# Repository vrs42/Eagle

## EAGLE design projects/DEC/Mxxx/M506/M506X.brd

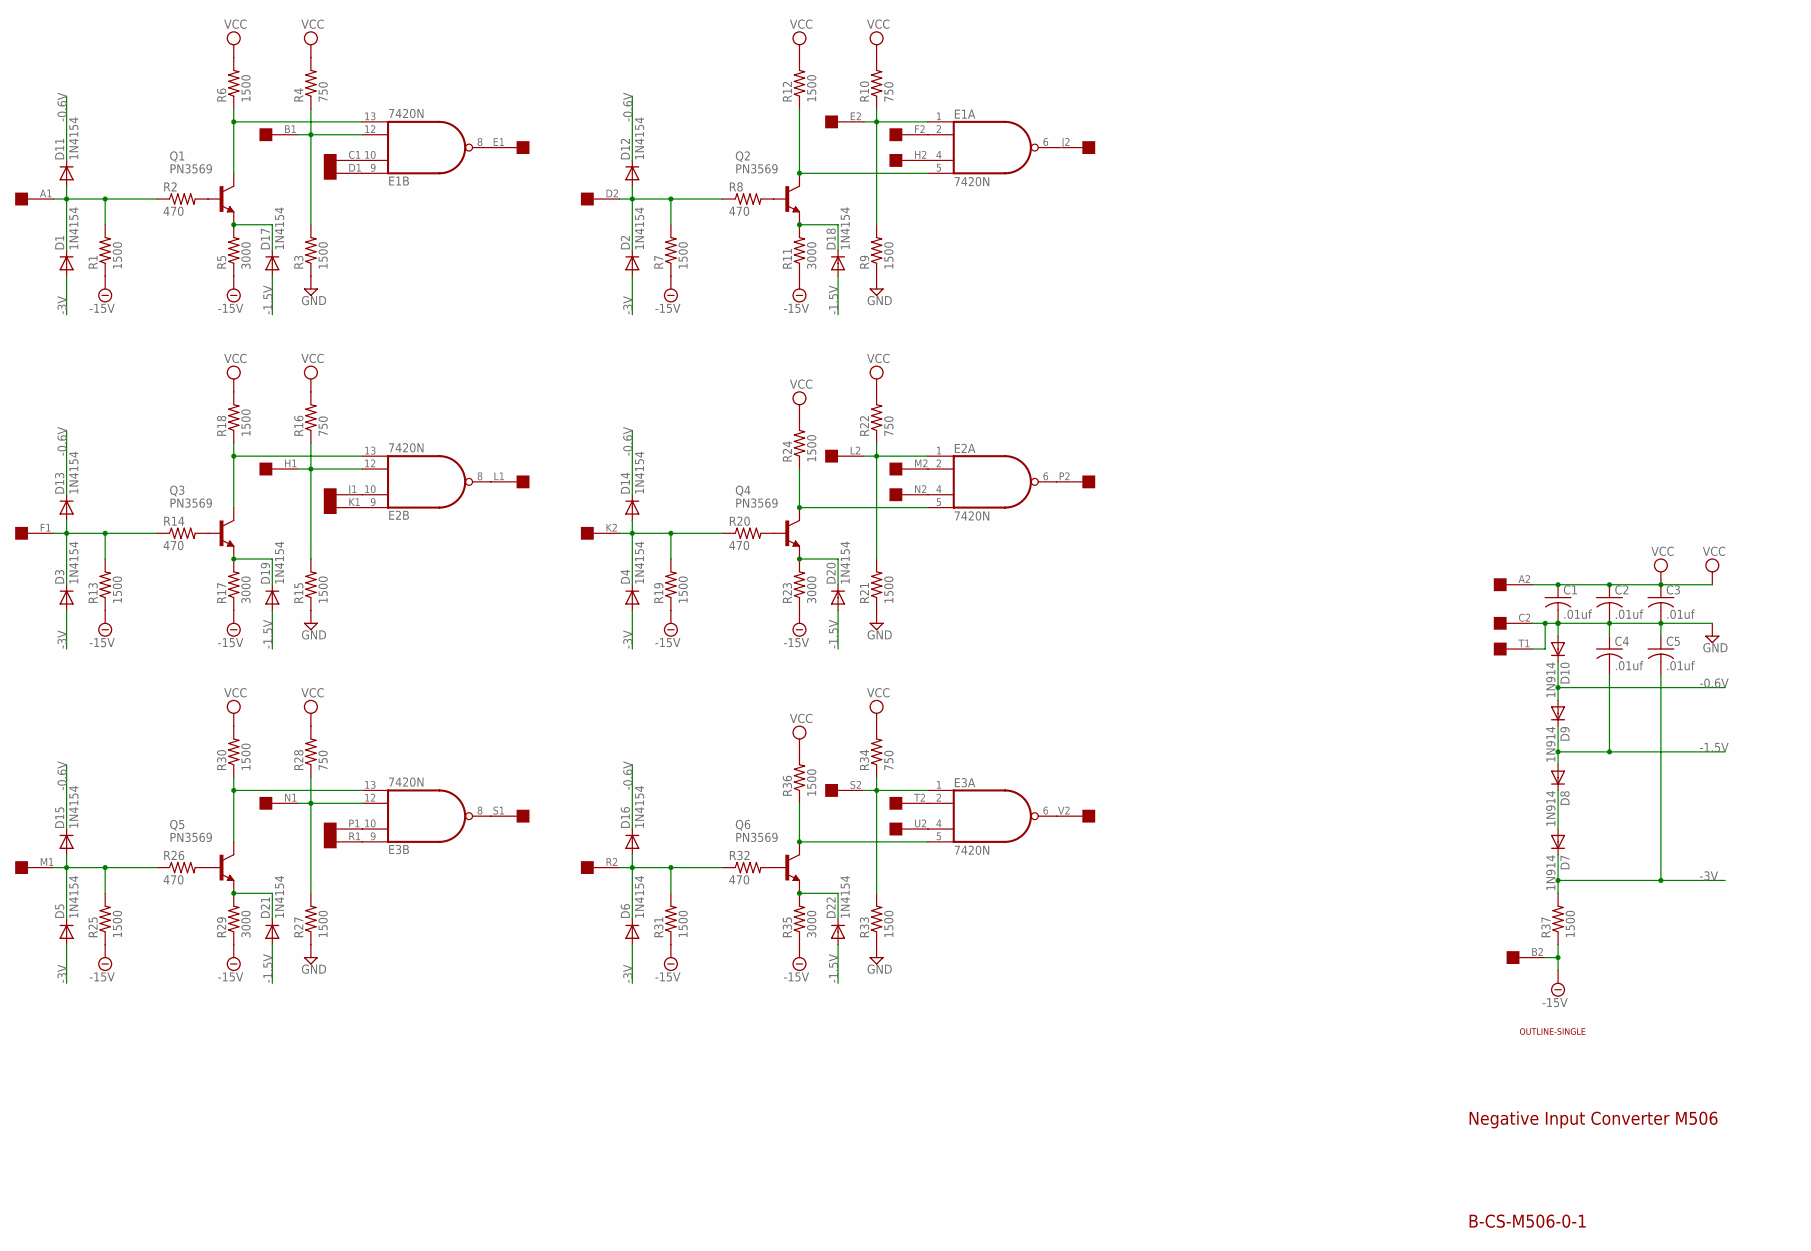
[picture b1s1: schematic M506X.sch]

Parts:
C1, C2, C3, C4, C5: .01uf; C050-025X075
D1, D2, D3, D4, D5, D6, D11, D12, D13, D14, D15, D16, D17, D18, D19, D20, D21, D22: 1N4154; DO35-10
D7, D8, D9, D10: 1N914; DO35-10
E1, E2, E3: 7420N; DIL14
Q1, Q2, Q3, Q4, Q5, Q6: PN3569; TO39
R1, R3, R6, R7, R9, R12, R13, R15, R18, R19, R21, R24, R25, R27, R30, R31, R33, R36, R37: 1500; 0207/10
R2, R8, R14, R20, R26, R32: 470; 0207/10
R4, R10, R16, R22, R28, R34: 750; 0207/10
R5, R11, R17, R23, R29, R35: 3000; 0207/10
U$2: SINGLE; EDGE-CON2
U$4: OUTLINE-SINGLE; SINGLE

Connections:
-0.6V: D9.A, D10.C, D11.C, D12.C, D13.C, D14.C, D15.C, D16.C
-1.5V: C4.2, D8.A, D9.C, D17.A, D18.A, D19.A, D20.A, D21.A, D22.A
-3V: C5.2, D1.A, D2.A, D3.A, D4.A, D5.A, D6.A, D7.C, R37.2
-15V: R1.1, R5.1, R7.1, R11.1, R13.1, R17.1, R19.1, R23.1, R25.1, R29.1, R31.1, R35.1, R37.1, U$2.B2
GND: C1.2, C2.2, C3.2, C4.1, C5.1, D10.A, E1.7 (GND), E2.7 (GND), E3.7 (GND), R3.1, R9.1, R15.1, R21.1, R27.1, R33.1, U$2.C2, U$2.T1
unnamed: D1.C, D11.A, R1.2, R2.1, U$2.A1
unnamed: Q1.2 (B), R2.2
unnamed: D17.C, Q1.1 (E), R5.2
unnamed: E1.12 (I2), R3.2, R4.1, U$2.B1
unnamed: E1.13 (I3), Q1.3 (C), R6.1
unnamed: E1.10 (I1), U$2.C1
unnamed: E1.9 (I0), U$2.D1
unnamed: E1.8 (O), U$2.E1
unnamed: D2.C, D12.A, R7.2, R8.1, U$2.D2
unnamed: Q2.2 (B), R8.2
unnamed: D18.C, Q2.1 (E), R11.2
unnamed: E1.1 (I0), R9.2, R10.1, U$2.E2
unnamed: E1.5 (I3), Q2.3 (C), R12.1
unnamed: E1.6 (O), U$2.J2
unnamed: E1.2 (I1), U$2.F2
unnamed: E1.4 (I2), U$2.H2
unnamed: D3.C, D13.A, R13.2, R14.1, U$2.F1
unnamed: Q3.2 (B), R14.2
unnamed: D19.C, Q3.1 (E), R17.2
unnamed: E2.12 (I2), R15.2, R16.1, U$2.H1
unnamed: E2.13 (I3), Q3.3 (C), R18.1
unnamed: D5.C, D15.A, R25.2, R26.1, U$2.M1
unnamed: Q5.2 (B), R26.2
unnamed: D21.C, Q5.1 (E), R29.2
unnamed: D4.C, D14.A, R19.2, R20.1, U$2.K2
unnamed: Q4.2 (B), R20.2
unnamed: D20.C, Q4.1 (E), R23.2
unnamed: E2.1 (I0), R21.2, R22.1, U$2.L2
unnamed: E2.5 (I3), Q4.3 (C), R24.1
unnamed: E3.12 (I2), R27.2, R28.1, U$2.N1
unnamed: E3.13 (I3), Q5.3 (C), R30.1
unnamed: D6.C, D16.A, R31.2, R32.1, U$2.R2
unnamed: Q6.2 (B), R32.2
unnamed: D22.C, Q6.1 (E), R35.2
unnamed: E3.1 (I0), R33.2, R34.1, U$2.S2
unnamed: E3.5 (I3), Q6.3 (C), R36.1
unnamed: E2.10 (I1), U$2.J1
unnamed: E2.9 (I0), U$2.K1
unnamed: E3.10 (I1), U$2.P1
unnamed: E3.9 (I0), U$2.R1
unnamed: E2.8 (O), U$2.L1
unnamed: E3.8 (O), U$2.S1
unnamed: E2.2 (I1), U$2.M2
unnamed: E2.4 (I2), U$2.N2
unnamed: E2.6 (O), U$2.P2
unnamed: E3.4 (I2), U$2.U2
unnamed: E3.6 (O), U$2.V2
unnamed: E3.2 (I1), U$2.T2
unnamed: D7.A, D8.C
VCC: C1.1, C2.1, C3.1, E1.14 (VCC), E2.14 (VCC), E3.14 (VCC), R4.2, R6.2, R10.2, R12.2, R16.2, R18.2, R22.2, R24.2, R28.2, R30.2, R34.2, R36.2, U$2.A2

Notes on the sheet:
Negative Input Converter M506
B-CS-M506-0-1

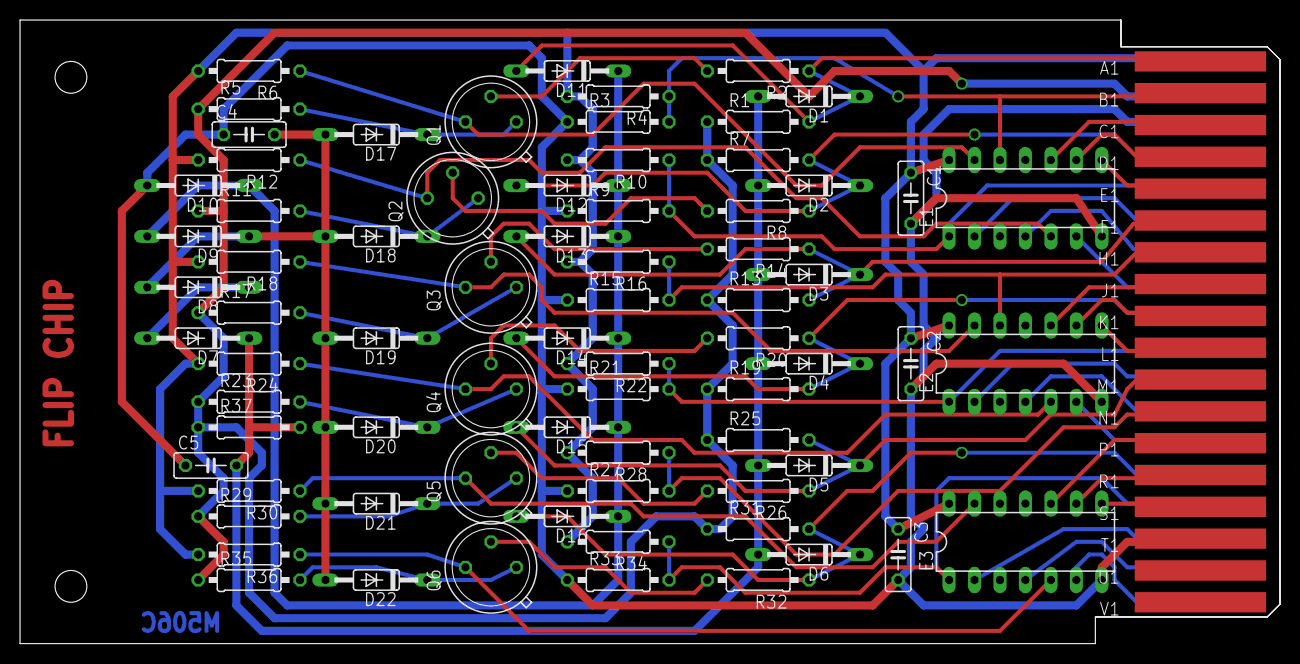
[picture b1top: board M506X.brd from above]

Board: 2 copper layers, 125.7 x 62.2 mm, 76 parts (0 on the bottom side), 55 nets.

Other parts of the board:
U$1: FLIPCHIP

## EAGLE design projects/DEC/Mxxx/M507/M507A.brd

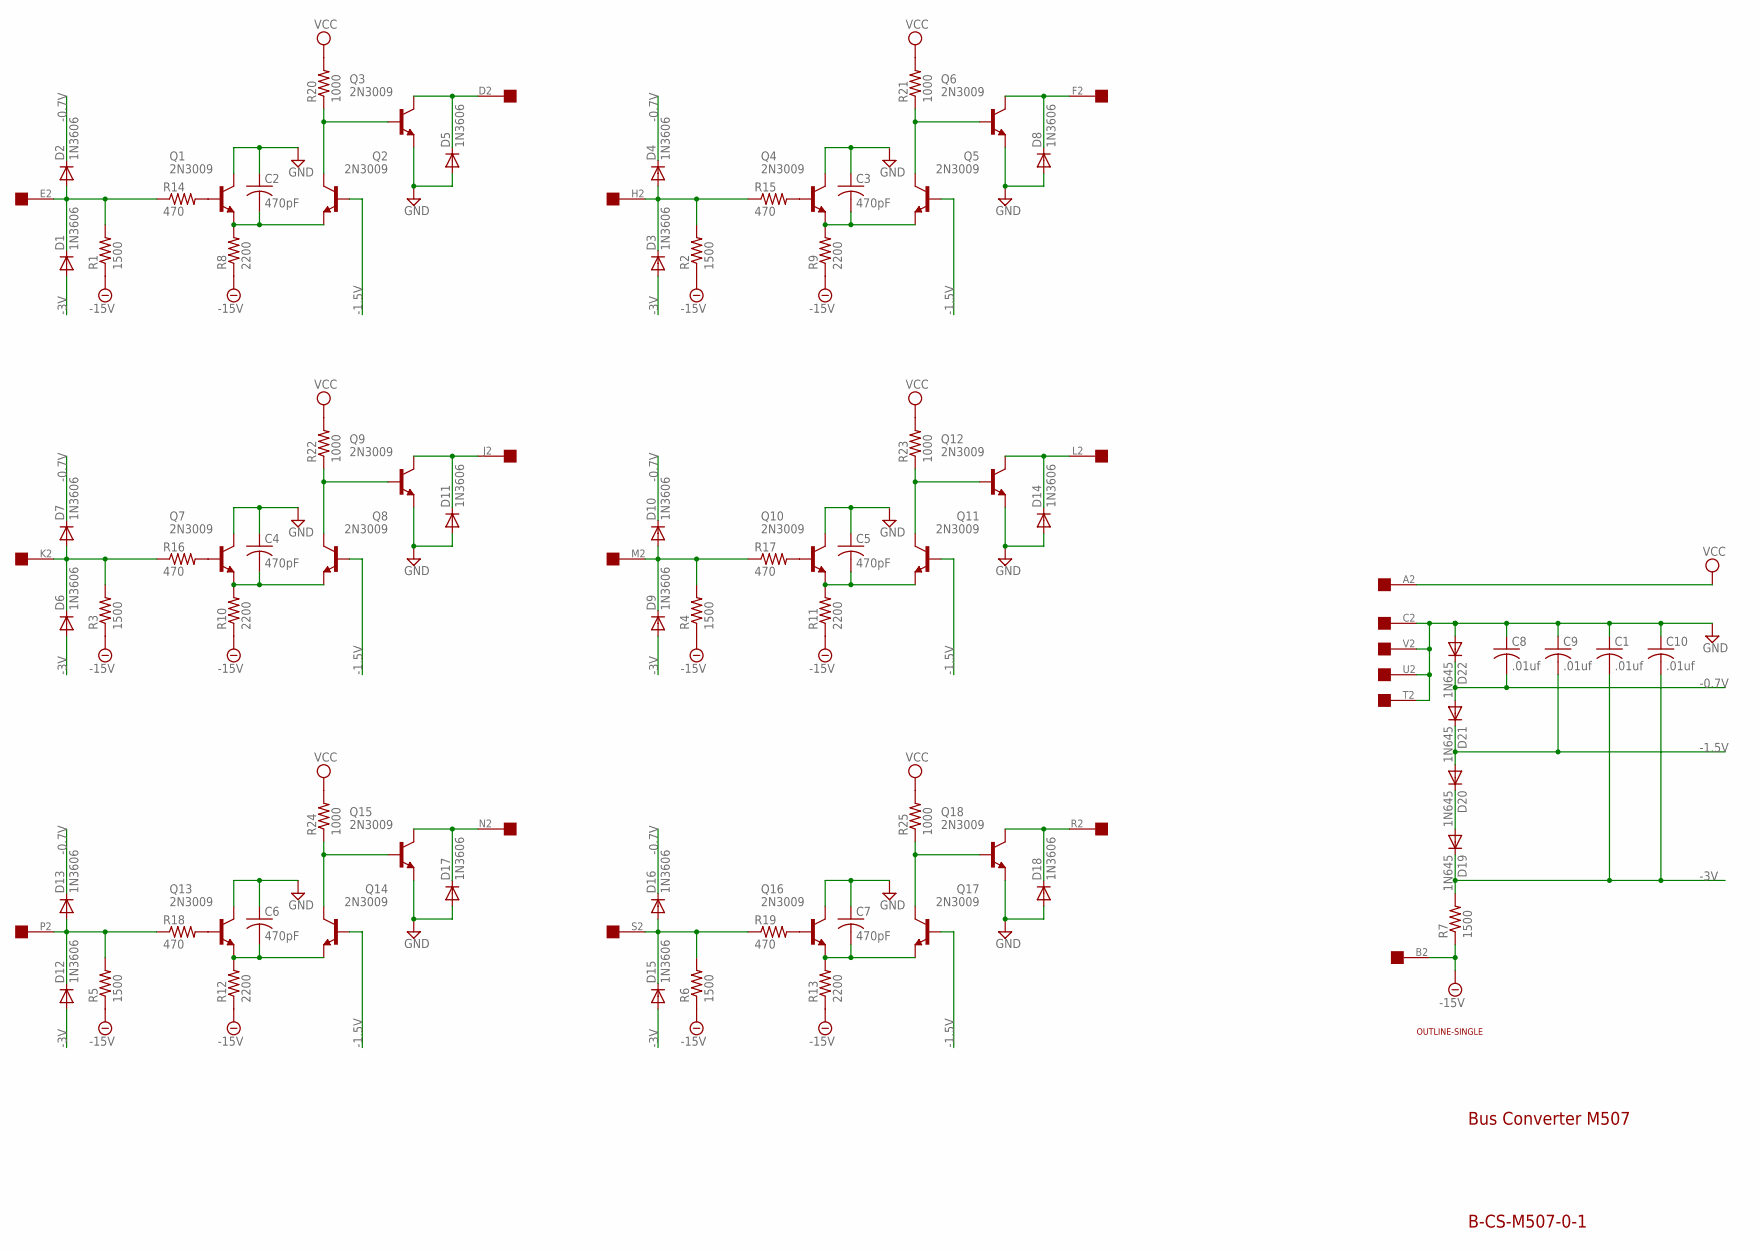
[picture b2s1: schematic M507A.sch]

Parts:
C1, C8, C9, C10: .01uf; C050-025X075
C2, C3, C4, C5, C6, C7: 470pF; C050-025X075
D1, D2, D3, D4, D5, D6, D7, D8, D9, D10, D11, D12, D13, D14, D15, D16, D17, D18: 1N3606; DO35-10
D19, D20, D21, D22: 1N645; DO35-10
Q1, Q2, Q3, Q4, Q5, Q6, Q7, Q8, Q9, Q10, Q11, Q12, Q13, Q14, Q15, Q16, Q17, Q18: 2N3009; TO39
R1, R2, R3, R4, R5, R6, R7: 1500; 0207/10
R8, R9, R10, R11, R12, R13: 2200; 0207/10
R14, R15, R16, R17, R18, R19: 470; 0207/10
R20, R21, R22, R23, R24, R25: 1000; 0207/10
U$3: EDGE-1; EDGE-CON1
U$4: OUTLINE-SINGLE; SINGLE

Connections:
-0.7V: C8.2, D2.C, D4.C, D7.C, D10.C, D13.C, D16.C, D21.A, D22.C
-1.5V: C9.2, D20.A, D21.C, Q2.2 (B), Q5.2 (B), Q8.2 (B), Q11.2 (B), Q14.2 (B), Q17.2 (B)
-3V: C1.2, C10.2, D1.A, D3.A, D6.A, D9.A, D12.A, D15.A, D19.C, R7.2
-15V: R1.1, R2.1, R3.1, R4.1, R5.1, R6.1, R7.1, R8.1, R9.1, R10.1, R11.1, R12.1, R13.1, U$3.B2
GND: C1.1, C2.1, C3.1, C4.1, C5.1, C6.1, C7.1, C8.1, C9.1, C10.1, D5.A, D8.A, D11.A, D14.A, D17.A, D18.A, D22.A, Q1.3 (C), Q3.1 (E), Q4.3 (C), Q6.1 (E), Q7.3 (C), Q9.1 (E), Q10.3 (C), Q12.1 (E), Q13.3 (C), Q15.1 (E), Q16.3 (C), Q18.1 (E), U$3.C2, U$3.T2, U$3.U2, U$3.V2
unnamed: D1.C, D2.A, R1.2, R14.1, U$3.E2
unnamed: Q1.2 (B), R14.2
unnamed: C2.2, Q1.1 (E), Q2.1 (E), R8.2
unnamed: D3.C, D4.A, R2.2, R15.1, U$3.H2
unnamed: Q2.3 (C), Q3.2 (B), R20.1
unnamed: D5.C, Q3.3 (C), U$3.D2
unnamed: Q4.2 (B), R15.2
unnamed: C3.2, Q4.1 (E), Q5.1 (E), R9.2
unnamed: Q5.3 (C), Q6.2 (B), R21.1
unnamed: D8.C, Q6.3 (C), U$3.F2
unnamed: D6.C, D7.A, R3.2, R16.1, U$3.K2
unnamed: Q7.2 (B), R16.2
unnamed: C4.2, Q7.1 (E), Q8.1 (E), R10.2
unnamed: Q8.3 (C), Q9.2 (B), R22.1
unnamed: D11.C, Q9.3 (C), U$3.J2
unnamed: D9.C, D10.A, R4.2, R17.1, U$3.M2
unnamed: Q10.2 (B), R17.2
unnamed: C5.2, Q10.1 (E), Q11.1 (E), R11.2
unnamed: Q11.3 (C), Q12.2 (B), R23.1
unnamed: D14.C, Q12.3 (C), U$3.L2
unnamed: D12.C, D13.A, R5.2, R18.1, U$3.P2
unnamed: Q13.2 (B), R18.2
unnamed: C6.2, Q13.1 (E), Q14.1 (E), R12.2
unnamed: Q14.3 (C), Q15.2 (B), R24.1
unnamed: D17.C, Q15.3 (C), U$3.N2
unnamed: D15.C, D16.A, R6.2, R19.1, U$3.S2
unnamed: Q16.2 (B), R19.2
unnamed: C7.2, Q16.1 (E), Q17.1 (E), R13.2
unnamed: Q17.3 (C), Q18.2 (B), R25.1
unnamed: D18.C, Q18.3 (C), U$3.R2
unnamed: D19.A, D20.C
VCC: R20.2, R21.2, R22.2, R23.2, R24.2, R25.2, U$3.A2

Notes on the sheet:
Bus Converter M507
B-CS-M507-0-1

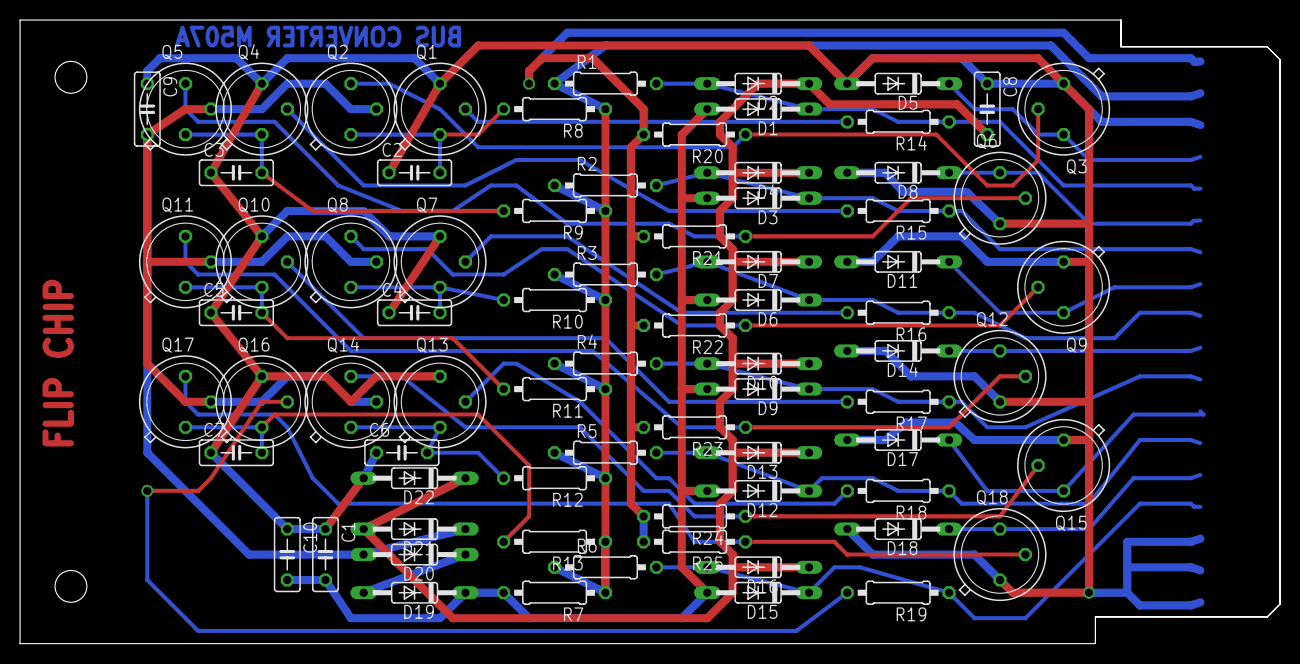
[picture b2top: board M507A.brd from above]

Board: 2 copper layers, 125.7 x 62.2 mm, 78 parts (0 on the bottom side), 37 nets.

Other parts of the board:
U$1: FLIPCHIP

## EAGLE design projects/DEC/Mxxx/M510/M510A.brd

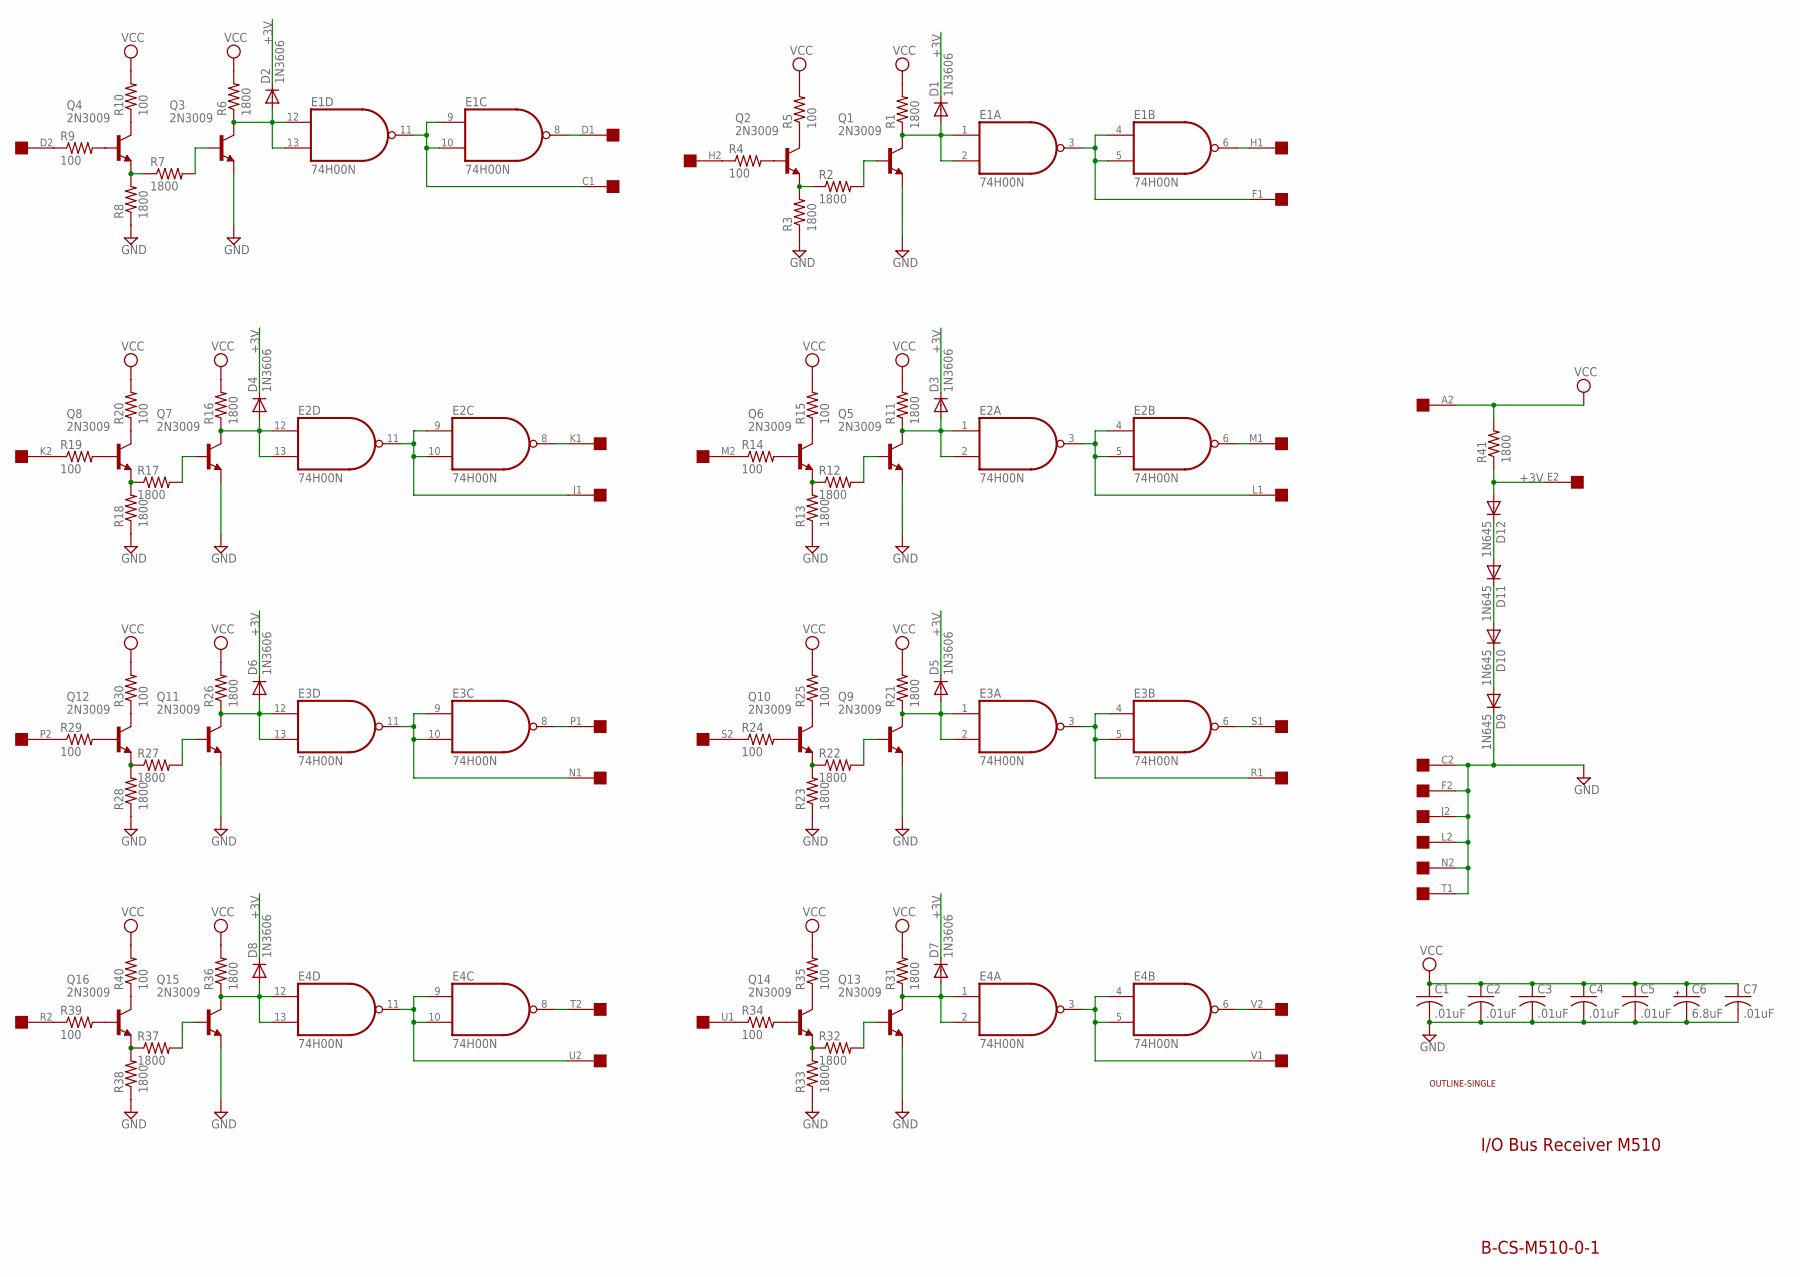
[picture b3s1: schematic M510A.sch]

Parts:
C1, C2, C3, C4, C5, C7: .01uF; C050-025X075
C6: 6.8uF; E12-8
D1, D2, D3, D4, D5, D6, D7, D8: 1N3606; DO35-10
D9, D10, D11, D12: 1N645; DO35-10
E1, E2, E3, E4: 74H00N; DIL14
EDGE1: EDGE-2CONNECTOR; EDGE-CON2
Q1, Q2, Q3, Q4, Q5, Q6, Q7, Q8, Q9, Q10, Q11, Q12, Q13, Q14, Q15, Q16: 2N3009; TO39
R1, R2, R3, R6, R7, R8, R11, R12, R13, R16, R17, R18, R21, R22, R23, R26, R27, R28, R31, R32, R33, R36, R37, R38, R41: 1800; 0207/10
R4, R5, R9, R10, R14, R15, R19, R20, R24, R25, R29, R30, R34, R35, R39, R40: 100; 0207/10
U$4: OUTLINE-SINGLE; SINGLE

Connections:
+3V: D1.C, D2.C, D3.C, D4.C, D5.C, D6.C, D7.C, D8.C, D12.A, EDGE1.E2, R41.1
GND: C1.2, C2.2, C3.2, C4.2, C5.2, C6.-, C7.2, D9.C, E1.7 (GND), E2.7 (GND), E3.7 (GND), E4.7 (GND), EDGE1.C2, EDGE1.F2, EDGE1.J2, EDGE1.L2, EDGE1.N2, EDGE1.T1, Q1.1 (E), Q3.1 (E), Q5.1 (E), Q7.1 (E), Q9.1 (E), Q11.1 (E), Q13.1 (E), Q15.1 (E), R3.1, R8.1, R13.1, R18.1, R23.1, R28.1, R33.1, R38.1
unnamed: EDGE1.D2, R9.1
unnamed: Q4.2 (B), R9.2
unnamed: Q3.2 (B), R7.2
unnamed: E1.9 (I0), E1.10 (I1), E1.11 (O), EDGE1.C1
unnamed: Q4.3 (C), R10.1
unnamed: D2.A, E1.12 (I0), E1.13 (I1), Q3.3 (C), R6.1
unnamed: EDGE1.H2, R4.1
unnamed: Q4.1 (E), R7.1, R8.2
unnamed: E1.8 (O), EDGE1.D1
unnamed: D11.A, D12.C
unnamed: D10.A, D11.C
unnamed: D3.A, E2.1 (I0), E2.2 (I1), Q5.3 (C), R11.1
unnamed: Q2.2 (B), R4.2
unnamed: D1.A, E1.1 (I0), E1.2 (I1), Q1.3 (C), R1.1
unnamed: E1.3 (O), E1.4 (I0), E1.5 (I1), EDGE1.F1
unnamed: Q1.2 (B), R2.2
unnamed: Q2.3 (C), R5.1
unnamed: Q2.1 (E), R2.1, R3.2
unnamed: E1.6 (O), EDGE1.H1
unnamed: E2.3 (O), E2.4 (I0), E2.5 (I1), EDGE1.L1
unnamed: Q5.2 (B), R12.2
unnamed: E2.6 (O), EDGE1.M1
unnamed: Q6.1 (E), R12.1, R13.2
unnamed: Q6.2 (B), R14.2
unnamed: Q6.3 (C), R15.1
unnamed: D4.A, E2.12 (I0), E2.13 (I1), Q7.3 (C), R16.1
unnamed: E2.9 (I0), E2.10 (I1), E2.11 (O), EDGE1.J1
unnamed: Q7.2 (B), R17.2
unnamed: E2.8 (O), EDGE1.K1
unnamed: Q8.1 (E), R17.1, R18.2
unnamed: Q8.2 (B), R19.2
unnamed: Q8.3 (C), R20.1
unnamed: D5.A, E3.1 (I0), E3.2 (I1), Q9.3 (C), R21.1
unnamed: E3.3 (O), E3.4 (I0), E3.5 (I1), EDGE1.R1
unnamed: Q9.2 (B), R22.2
unnamed: E3.6 (O), EDGE1.S1
unnamed: Q10.1 (E), R22.1, R23.2
unnamed: Q10.2 (B), R24.2
unnamed: Q10.3 (C), R25.1
unnamed: D6.A, E3.12 (I0), E3.13 (I1), Q11.3 (C), R26.1
unnamed: E3.9 (I0), E3.10 (I1), E3.11 (O), EDGE1.N1
unnamed: Q11.2 (B), R27.2
unnamed: E3.8 (O), EDGE1.P1
unnamed: Q12.1 (E), R27.1, R28.2
unnamed: Q12.2 (B), R29.2
unnamed: Q12.3 (C), R30.1
unnamed: EDGE1.K2, R19.1
unnamed: EDGE1.M2, R14.1
unnamed: D7.A, E4.1 (I0), E4.2 (I1), Q13.3 (C), R31.1
unnamed: D9.A, D10.C
unnamed: E4.3 (O), E4.4 (I0), E4.5 (I1), EDGE1.V1
unnamed: Q13.2 (B), R32.2
unnamed: E4.6 (O), EDGE1.V2
unnamed: Q14.1 (E), R32.1, R33.2
unnamed: Q14.2 (B), R34.2
unnamed: Q14.3 (C), R35.1
unnamed: D8.A, E4.12 (I0), E4.13 (I1), Q15.3 (C), R36.1
unnamed: E4.9 (I0), E4.10 (I1), E4.11 (O), EDGE1.U2
unnamed: Q15.2 (B), R37.2
unnamed: E4.8 (O), EDGE1.T2
unnamed: Q16.1 (E), R37.1, R38.2
unnamed: Q16.2 (B), R39.2
unnamed: Q16.3 (C), R40.1
unnamed: EDGE1.P2, R29.1
unnamed: EDGE1.S2, R24.1
unnamed: EDGE1.R2, R39.1
unnamed: EDGE1.U1, R34.1
VCC: C1.1, C2.1, C3.1, C4.1, C5.1, C6.+, C7.1, E1.14 (VCC), E2.14 (VCC), E3.14 (VCC), E4.14 (VCC), EDGE1.A2, R1.2, R5.2, R6.2, R10.2, R11.2, R15.2, R16.2, R20.2, R21.2, R25.2, R26.2, R30.2, R31.2, R35.2, R36.2, R40.2, R41.2

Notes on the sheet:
I/O Bus Receiver M510
B-CS-M510-0-1

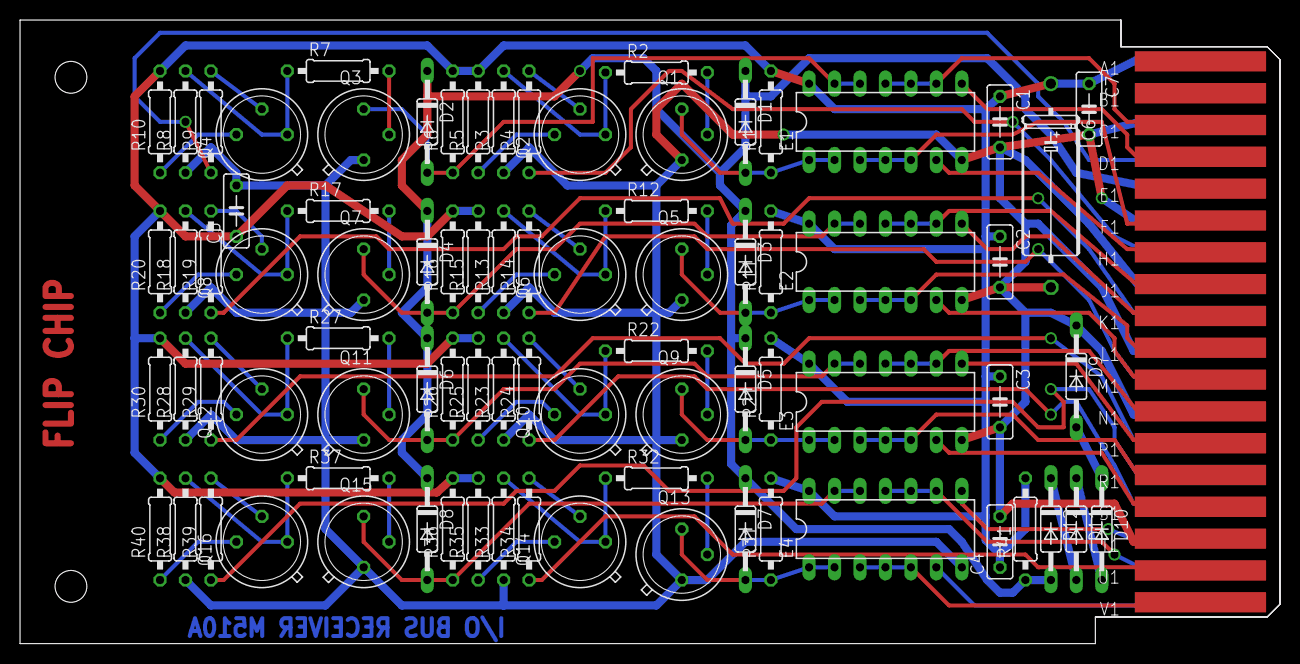
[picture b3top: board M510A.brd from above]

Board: 2 copper layers, 125.7 x 62.2 mm, 83 parts (0 on the bottom side), 70 nets.

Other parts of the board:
U$1: FLIPCHIP

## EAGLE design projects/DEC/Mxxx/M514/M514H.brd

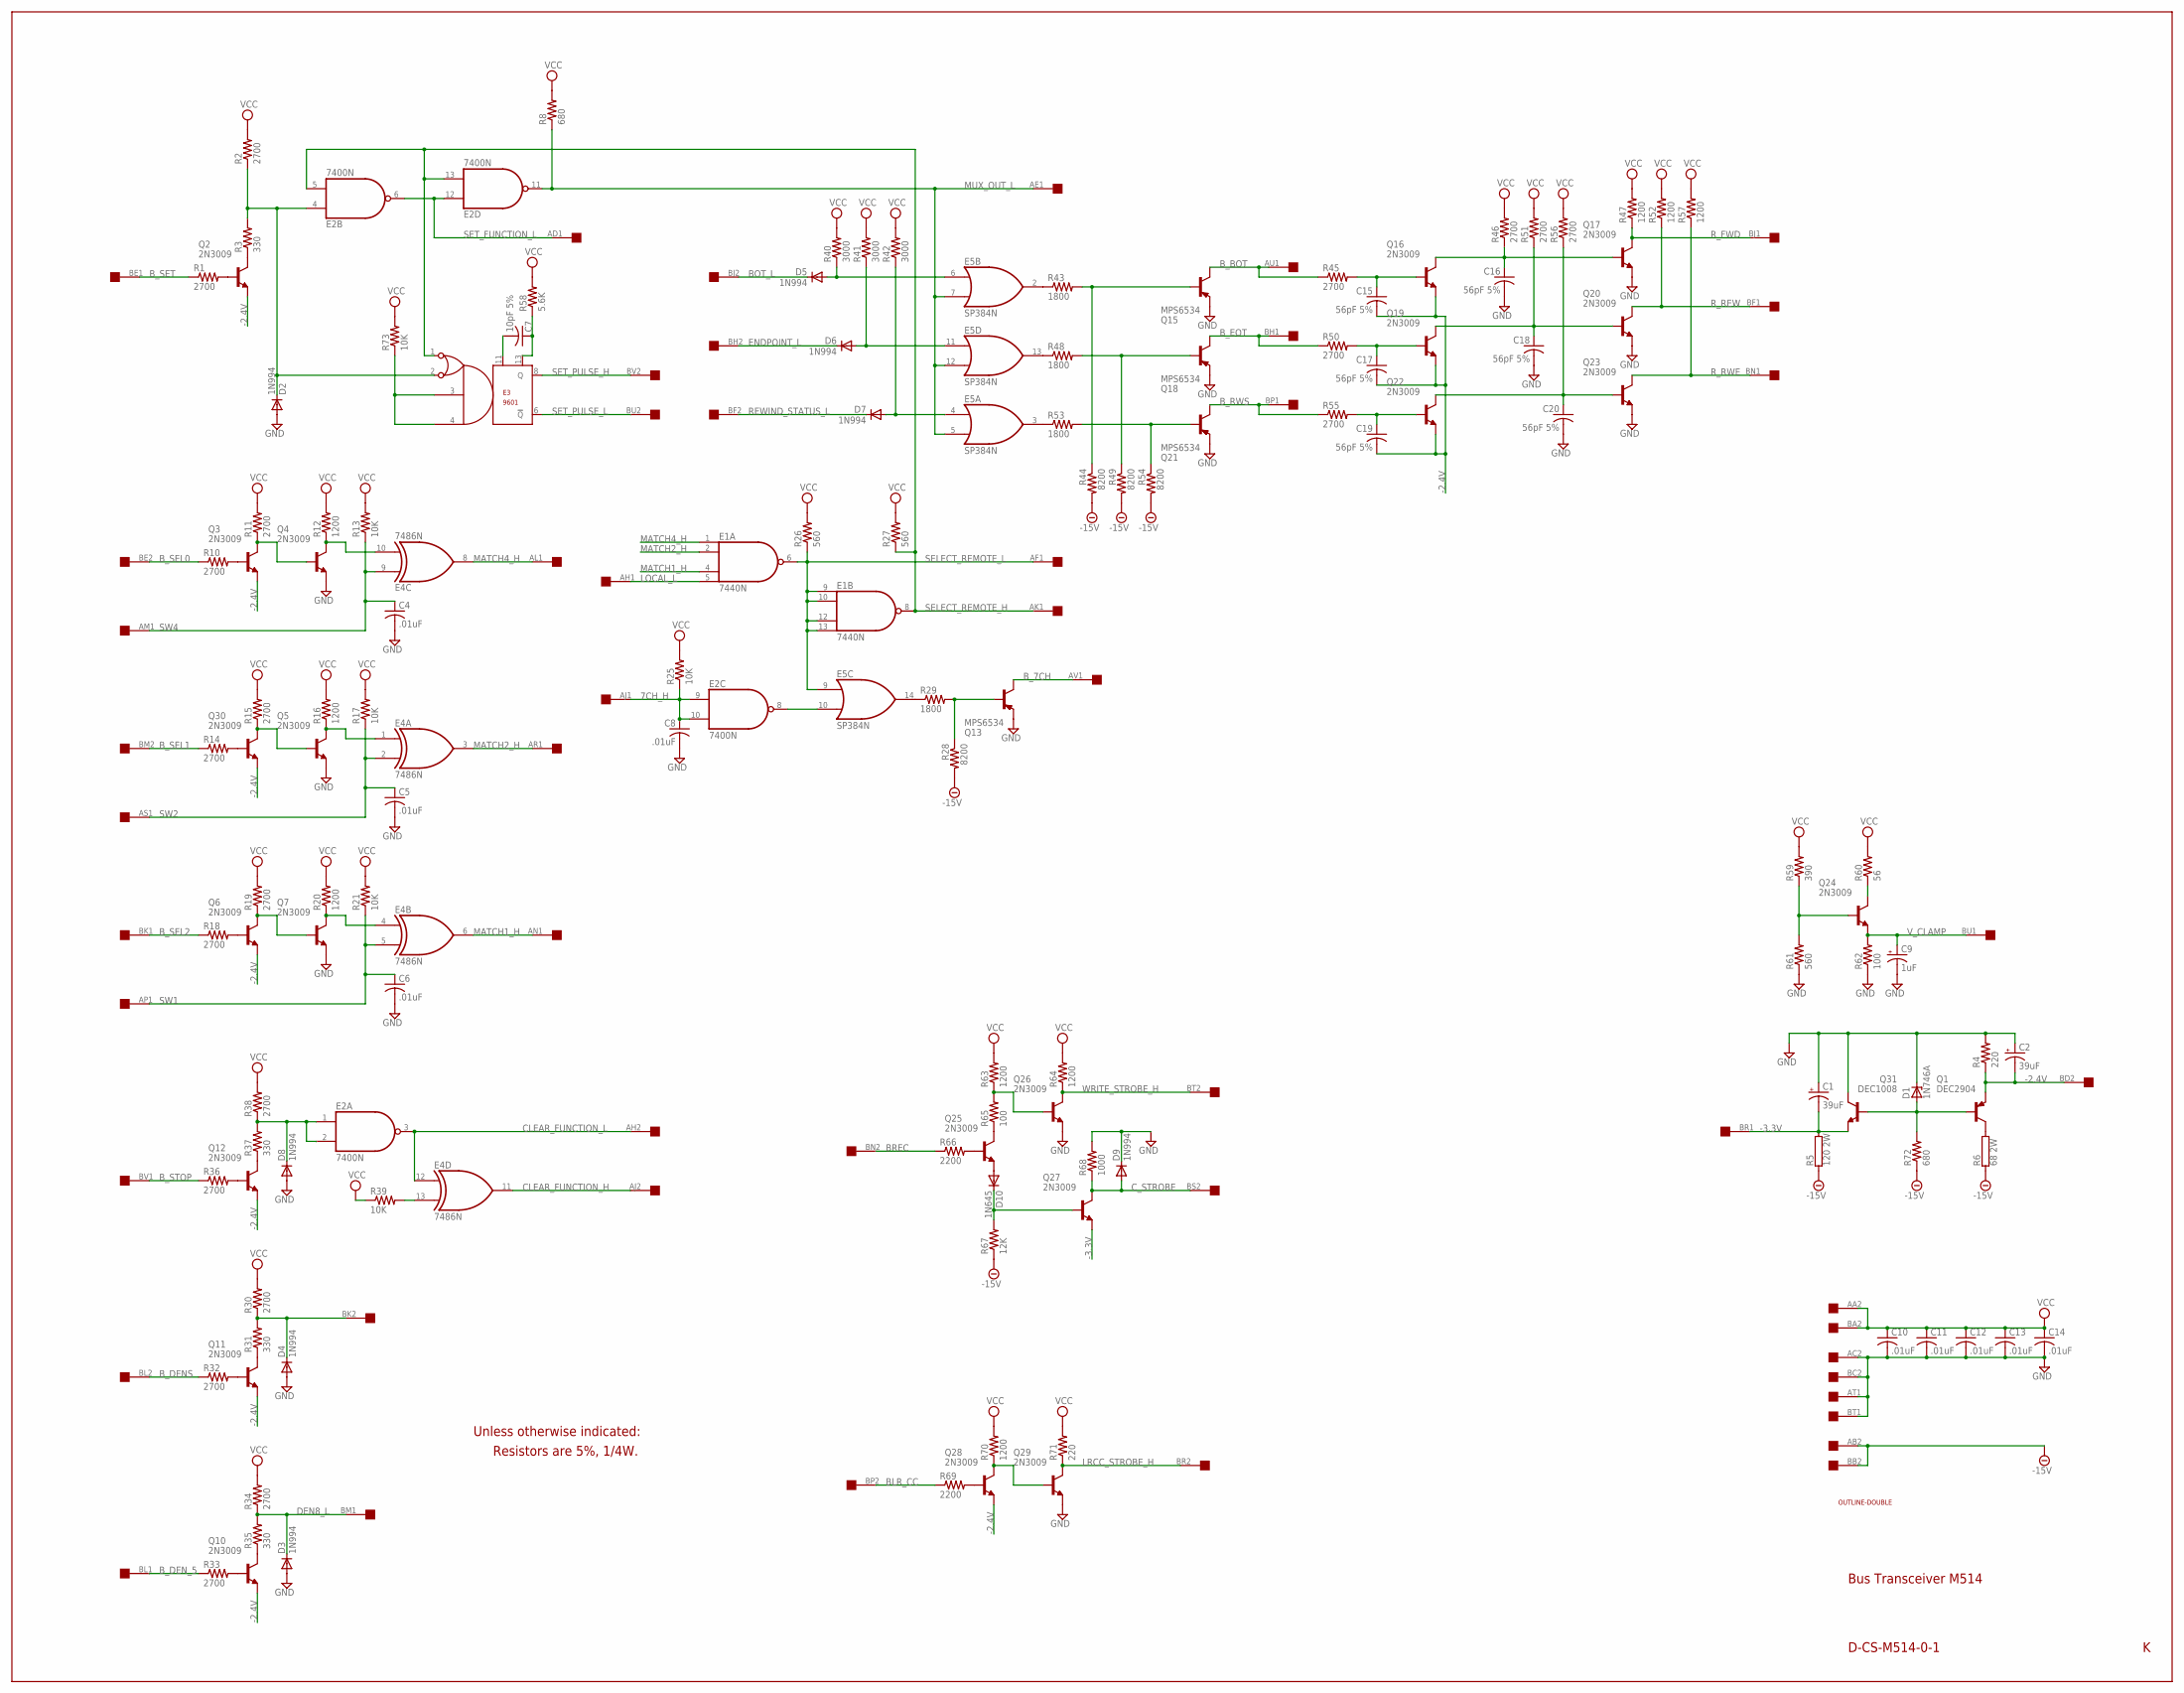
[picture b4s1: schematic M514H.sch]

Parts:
C1, C2: 39uF; E12-8
C4, C5, C6, C8, C10, C11, C12, C13, C14: .01uF; C050-025X075
C7: 10pF 5%; C050-025X075
C9: 1uF; E15-5
C15, C16, C17, C18, C19, C20: 56pF 5%; C050-025X075
D1: 1N746A; DO35Z10
D2, D3, D4, D5, D6, D7, D8, D9: 1N994; DO35-10
D10: 1N645; DO35-10
E1: 7440N; DIL14
E2: 7400N; DIL14
E3: 9601; DIL14
E4: 7486N; DIL14
E5: SP384N; DIL14
Q1: DEC2904; TO39
Q2, Q3, Q4, Q5, Q6, Q7, Q10, Q11, Q12, Q16, Q17, Q19, Q20, Q22, Q23, Q24, Q25, Q26, Q27, Q28, Q29, Q30: 2N3009; TO5
Q13, Q15, Q18, Q21: MPS6534; TO39
Q31: DEC1008; TO5
R1, R2, R10, R11, R14, R15, R18, R19, R30, R32, R33, R34, R36, R38, R45, R46, R50, R51, R55, R56: 2700; 0207/10
R3, R31, R35, R37: 330; 0207/10
R4, R71: 220; 0207/10
R5: 120 2W; KH206-8
R6: 68 2W; KH206-8
R8, R72: 680; 0207/10
R12, R16, R20, R47, R52, R57, R63, R64, R70: 1200; 0207/10
R13, R17, R21, R25, R39, R73: 10K; 0207/10
R26, R27, R61: 560; 0207/10
R28, R44, R49, R54: 8200; 0207/10
R29, R43, R48, R53: 1800; 0207/10
R40, R41, R42: 3000; 0207/10
R58: 5.6K; 0207/10
R59: 390; 0207/10
R60: 56; 0207/10
R62, R65: 100; 0207/10
R66, R69: 2200; 0207/10
R67: 12K; 0207/10
R68: 1000; 0207/10
U$1: DOUBLE; EDGE-CON4
U$2: OUTLINE-DOUBLE; DOUBLE

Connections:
7CH_H: C8.1, E2.9 (I0), E2.10 (I1), R25.1, U$1.AJ1
-2.4V: C2.-, C15.2, C17.2, C19.2, Q1.1 (E), Q2.1 (E), Q3.1 (E), Q6.1 (E), Q10.1 (E), Q11.1 (E), Q12.1 (E), Q16.1 (E), Q19.1 (E), Q22.1 (E), Q28.1 (E), Q30.1 (E), R4.1, U$1.BD2
-3.3V: C1.-, Q27.1 (E), Q31.1 (E), R5.2, U$1.BR1
-15V: R5.1, R6.1, R28.2, R44.2, R49.2, R54.2, R67.1, R72.1, U$1.AB2, U$1.BB2
BLR_CC: R69.1, U$1.BP2
BOT_L: D5.C, U$1.BJ2
BREC: R66.1, U$1.BN2
B_7CH: Q13.3 (C), U$1.AV1
B_BOT: Q15.3 (C), R45.1, U$1.AU1
B_DENS: R32.1, U$1.BL2
B_DEN_5: R33.1, U$1.BL1
B_EOT: Q18.3 (C), R50.1, U$1.BH1
B_RWS: Q21.3 (C), R55.1, U$1.BP1
B_SEL0: R10.1, U$1.BE2
B_SEL1: R14.1, U$1.BM2
B_SEL2: R18.1, U$1.BK1
B_SET: R1.1, U$1.BE1
B_STOP: R36.1, U$1.BV1
CLEAR_FUNCTION_H: E4.11 (O), U$1.AJ2
CLEAR_FUNCTION_L: E2.3 (O), E4.12 (I0), U$1.AH2
C_STROBE: D9.A, Q27.3 (C), R68.1, U$1.BS2
DEN8_L: D3.C, R34.1, R35.2, U$1.BM1
ENDPOINT_L: D6.C, U$1.BH2
GND: C1.+, C2.+, C4.2, C5.2, C6.2, C8.2, C9.-, C10.2, C11.2, C12.2, C13.2, C14.2, C16.2, C18.2, C20.2, D1.C, D2.A, D3.A, D4.A, D8.A, D9.C, E1.7 (GND), E2.7 (GND), E3.7 (GND), E4.7 (GND), E5.1 (GND), Q4.1 (E), Q5.1 (E), Q7.1 (E), Q13.1 (E), Q15.1 (E), Q17.1 (E), Q18.1 (E), Q20.1 (E), Q21.1 (E), Q23.1 (E), Q26.1 (E), Q29.1 (E), Q31.3 (C), R4.2, R61.1, R62.1, R68.2, U$1.AC2, U$1.AT1, U$1.BC2, U$1.BT1
LOCAL_L: E1.5 (I3), U$1.AH1
LRCC_STROBE_H: Q29.3 (C), R71.1, U$1.BR2
MATCH1_H: E1.4 (I2), E4.6 (O), U$1.AN1
MATCH2_H: E1.2 (I1), E4.3 (O), U$1.AR1
MATCH4_H: E1.1 (I0), E4.8 (O), U$1.AL1
MUX_OUT_L: E2.11 (O), E5.5 (I1), E5.7 (I1), E5.12 (I1), R8.1, U$1.AE1
unnamed: C7.1, E3.13, R58.1
unnamed: Q2.3 (C), R3.1
unnamed: Q2.2 (B), R1.2
unnamed: D2.C, E2.4 (I0), E3.2, R2.1, R3.2
unnamed: E3.3, E3.4, R73.1
unnamed: C7.2, E3.11
unnamed: Q1.3 (C), R6.2
unnamed: D1.A, Q1.2 (B), Q31.2 (B), R72.2
unnamed: Q3.2 (B), R10.2
unnamed: E2.8 (O), E5.10 (I1)
unnamed: Q3.3 (C), Q4.2 (B), R11.1
unnamed: E4.10 (I1), Q4.3 (C), R12.1
unnamed: Q12.2 (B), R36.2
unnamed: Q30.2 (B), R14.2
unnamed: Q5.2 (B), Q30.3 (C), R15.1
unnamed: E4.1 (I0), Q5.3 (C), R16.1
unnamed: Q6.2 (B), R18.2
unnamed: Q6.3 (C), Q7.2 (B), R19.1
unnamed: E4.4 (I0), Q7.3 (C), R20.1
unnamed: Q12.3 (C), R37.1
unnamed: D5.A, E5.6 (I0), R40.1
unnamed: D8.C, E2.1 (I0), E2.2 (I1), R37.2, R38.1
unnamed: Q11.3 (C), R31.1
unnamed: D6.A, E5.11 (I0), R41.1
unnamed: Q11.2 (B), R32.2
unnamed: D4.C, R30.1, R31.2, U$1.BK2
unnamed: Q10.3 (C), R35.1
unnamed: D7.A, E5.4 (I0), R42.1
unnamed: Q10.2 (B), R33.2
unnamed: E5.2 (O), R43.1
unnamed: E5.13 (O), R48.1
unnamed: E5.3 (O), R53.1
unnamed: E5.14 (O), R29.1
unnamed: Q13.2 (B), R28.1, R29.2
unnamed: Q15.2 (B), R43.2, R44.1
unnamed: Q18.2 (B), R48.2, R49.1
unnamed: Q21.2 (B), R53.2, R54.1
unnamed: E4.13 (I1), R39.2
unnamed: C19.1, Q22.2 (B), R55.2
unnamed: C17.1, Q19.2 (B), R50.2
unnamed: C15.1, Q16.2 (B), R45.2
unnamed: Q28.2 (B), R69.2
unnamed: Q24.2 (B), R59.1, R61.2
unnamed: Q24.3 (C), R60.1
unnamed: C20.1, Q22.3 (C), Q23.2 (B), R56.1
unnamed: C16.1, Q16.3 (C), Q17.2 (B), R46.1
unnamed: C18.1, Q19.3 (C), Q20.2 (B), R51.1
unnamed: Q28.3 (C), Q29.2 (B), R70.1
unnamed: Q25.2 (B), R66.2
unnamed: D10.A, Q25.1 (E)
unnamed: D10.C, Q27.2 (B), R67.2
unnamed: Q25.3 (C), R65.1
unnamed: Q26.2 (B), R63.1, R65.2
REWIND_STATUS_L: D7.C, U$1.BF2
R_FWD: Q17.3 (C), R47.1, U$1.BJ1
R_REW: Q20.3 (C), R52.1, U$1.BF1
R_RWE: Q23.3 (C), R57.1, U$1.BN1
SELECT_REMOTE_H: E1.8 (O), E2.5 (I1), E2.13 (I1), E3.1, R27.1, U$1.AK1
SELECT_REMOTE_L: E1.6 (O), E1.9 (I0), E1.10 (I1), E1.12 (I2), E1.13 (I3), E5.9 (I0), R26.1, U$1.AF1
SET_FUNCTION_L: E2.6 (O), E2.12 (I0), U$1.AD1
SET_PULSE_H: E3.8 (Q), U$1.BV2
SET_PULSE_L: E3.6 (!Q), U$1.BU2
SW1: C6.1, E4.5 (I1), R21.1, U$1.AP1
SW2: C5.1, E4.2 (I1), R17.1, U$1.AS1
SW4: C4.1, E4.9 (I0), R13.1, U$1.AM1
VCC: C10.1, C11.1, C12.1, C13.1, C14.1, E1.14 (VCC), E2.14 (VCC), E3.14 (VCC), E4.14 (VCC), E5.8 (VCC), R2.2, R8.2, R11.2, R12.2, R13.2, R15.2, R16.2, R17.2, R19.2, R20.2, R21.2, R25.2, R26.2, R27.2, R30.2, R34.2, R38.2, R39.1, R40.2, R41.2, R42.2, R46.2, R47.2, R51.2, R52.2, R56.2, R57.2, R58.2, R59.2, R60.2, R63.2, R64.2, R70.2, R71.2, R73.2, U$1.AA2, U$1.BA2
V_CLAMP: C9.+, Q24.1 (E), R62.2, U$1.BU1
WRITE_STROBE_H: Q26.3 (C), R64.1, U$1.BT2

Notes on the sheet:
Bus Transceiver M514
D-CS-M514-0-1
Unless otherwise indicated:
Resistors are 5%, 1/4W.
